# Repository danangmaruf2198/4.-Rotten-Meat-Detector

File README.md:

# 4.-Rotten-Meat-Detector
this project is about rotten meat detector, based on arduino with tcs3200 sensor and also there is some button an lcd used as interface. this project will make some scoring for each meat that detected by the sensor, and then the sensor will make some score for the meat and also classifying the meat. is that in a safe meat which still can be eaten or the rotten meat.

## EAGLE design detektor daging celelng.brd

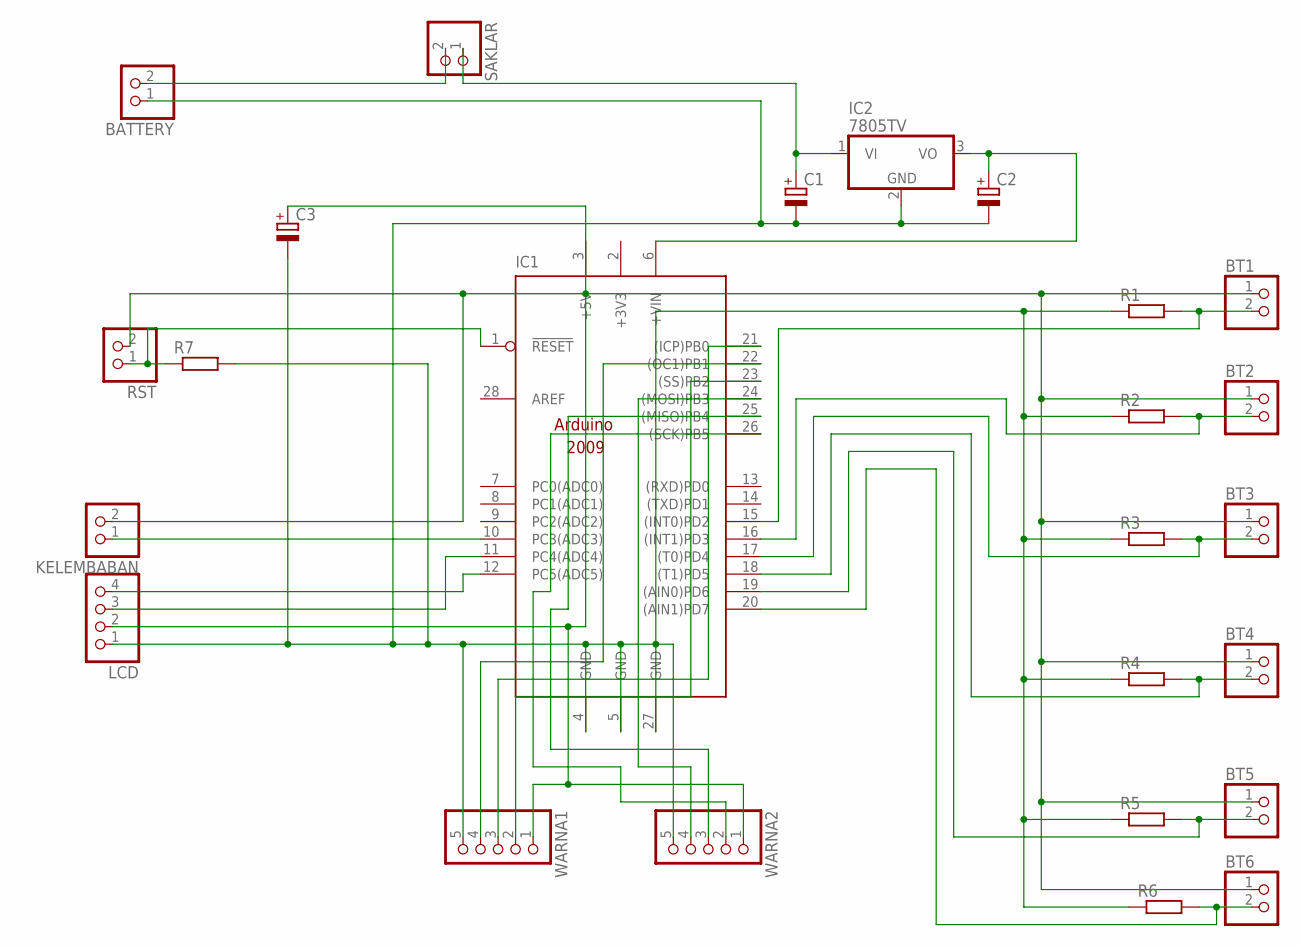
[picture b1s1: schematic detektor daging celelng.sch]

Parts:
BATTERY: PINHD-1X2; 1X02
BT1, BT2, BT3, BT4, BT5, BT6: PINHD-1X2; 1X02
C1, C2, C3: CPOL-EUE2.5-7; E2,5-7
IC1: ARDUINO2009_PIN_10; ARDUINO2009
IC2: 7805TV; TO220V
KELEMBABAN: PINHD-1X2; 1X02
LCD: PINHD-1X4; 1X04
R1, R2, R3, R4, R5, R6, R7: R-EU_0207/10; 0207/10
RST: PINHD-1X2; 1X02
SAKLAR: PINHD-1X2; 1X02
WARNA1, WARNA2: PINHD-1X5; 1X05

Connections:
+3V3: IC1.2 (+3V3)
unnamed: BT1.1, BT2.1, BT3.1, BT4.1, BT5.1, BT6.1, C3.+, IC1.3 (+5V), KELEMBABAN.2, LCD.2, RST.2, WARNA1.1, WARNA2.1
unnamed: BT3.2, IC1.17 ((T0)PD4), R3.2
unnamed: BT4.2, IC1.18 ((T1)PD5), R4.2
unnamed: BT2.2, IC1.16 ((INT1)PD3), R2.2
unnamed: BT1.2, IC1.15 ((INT0)PD2), R1.2
unnamed: BT5.2, IC1.19 ((AIN0)PD6), R5.2
unnamed: BT6.2, IC1.20 ((AIN1)PD7), R6.2
unnamed: IC1.12 (PC5(ADC5)), LCD.4
unnamed: IC1.11 (PC4(ADC4)), LCD.3
unnamed: C1.+, IC2.1 (VI), SAKLAR.1
unnamed: C2.+, IC1.6 (+VIN), IC2.3 (VO)
unnamed: BATTERY.1, C1.-, C2.-, C3.-, IC1.4 (GND), IC1.5 (GND), IC1.27 (GND), IC2.2 (GND), LCD.1, R1.1, R2.1, R3.1, R4.1, R5.1, R6.1, R7.2, WARNA1.5, WARNA2.5
unnamed: IC1.22 ((OC1)PB1), WARNA1.4
unnamed: IC1.21 ((ICP)PB0), WARNA1.3
unnamed: IC1.23 ((SS)PB2), WARNA1.2
unnamed: IC1.24 ((MOSI)PB3), WARNA2.4
unnamed: IC1.25 ((MISO)PB4), WARNA2.3
unnamed: IC1.26 ((SCK)PB5), WARNA2.2
unnamed: IC1.10 (PC3(ADC3)), KELEMBABAN.1
unnamed: BATTERY.2, SAKLAR.2
unnamed: IC1.1 (!RESET), R7.1, RST.1

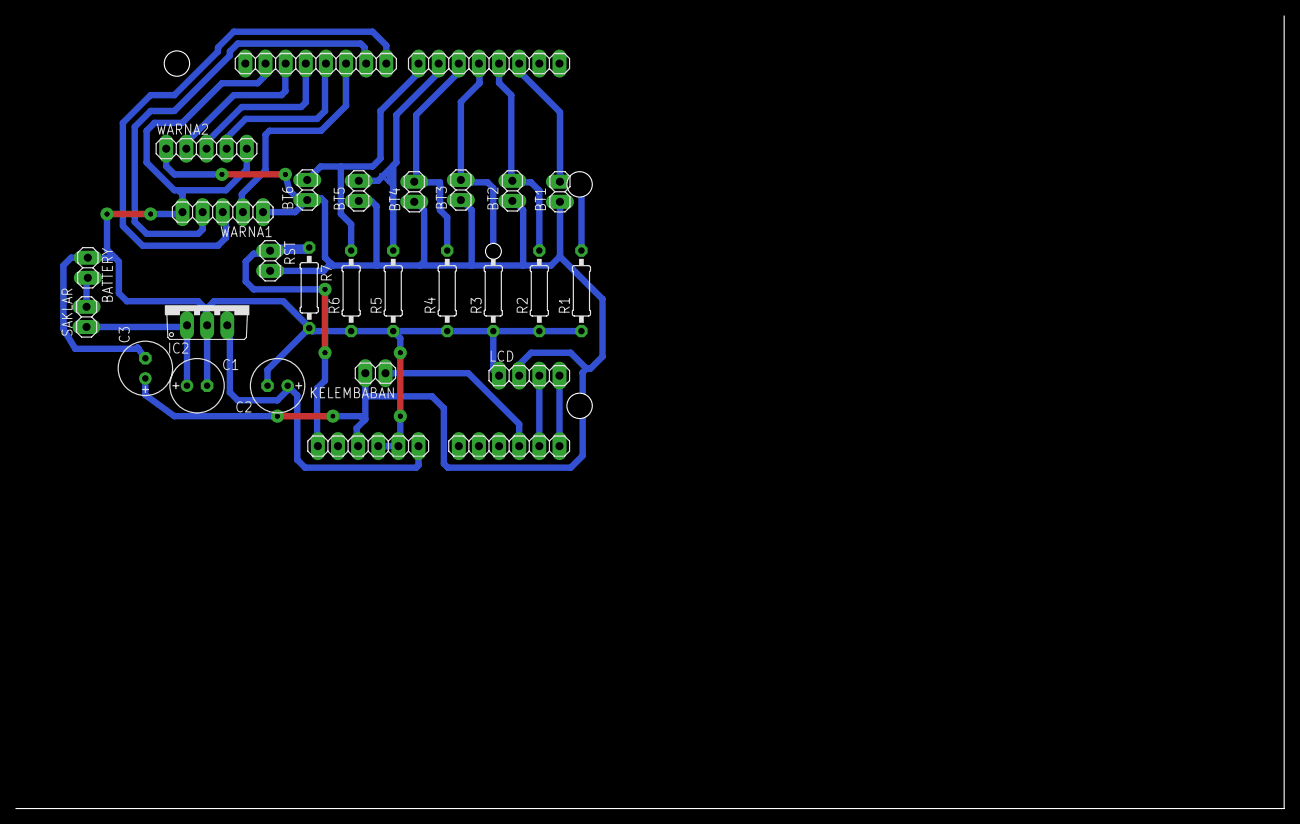
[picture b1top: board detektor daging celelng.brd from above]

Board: 2 copper layers, 160.0 x 100.0 mm, 25 parts (0 on the bottom side), 21 nets.
